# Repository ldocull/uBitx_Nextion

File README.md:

# uBitx_Nextion
This PCBA cleans up the wiring for V3-V5 uBitx Radio Kits that use the Nextion Display

Key features are:

 - [KB8CEC](https://github.com/phdlee) signal level meter and DSP functions are incorporated.
 - Anti-pop circuit was added to reduce the magnitude of key-clicks
 - Additional power supply filtering reduces background audio noise
 - Convenient points of connection for the Nextion display
 - Intermediate connections reduce wire harness

-[WR9R](http://wr9r.com/)

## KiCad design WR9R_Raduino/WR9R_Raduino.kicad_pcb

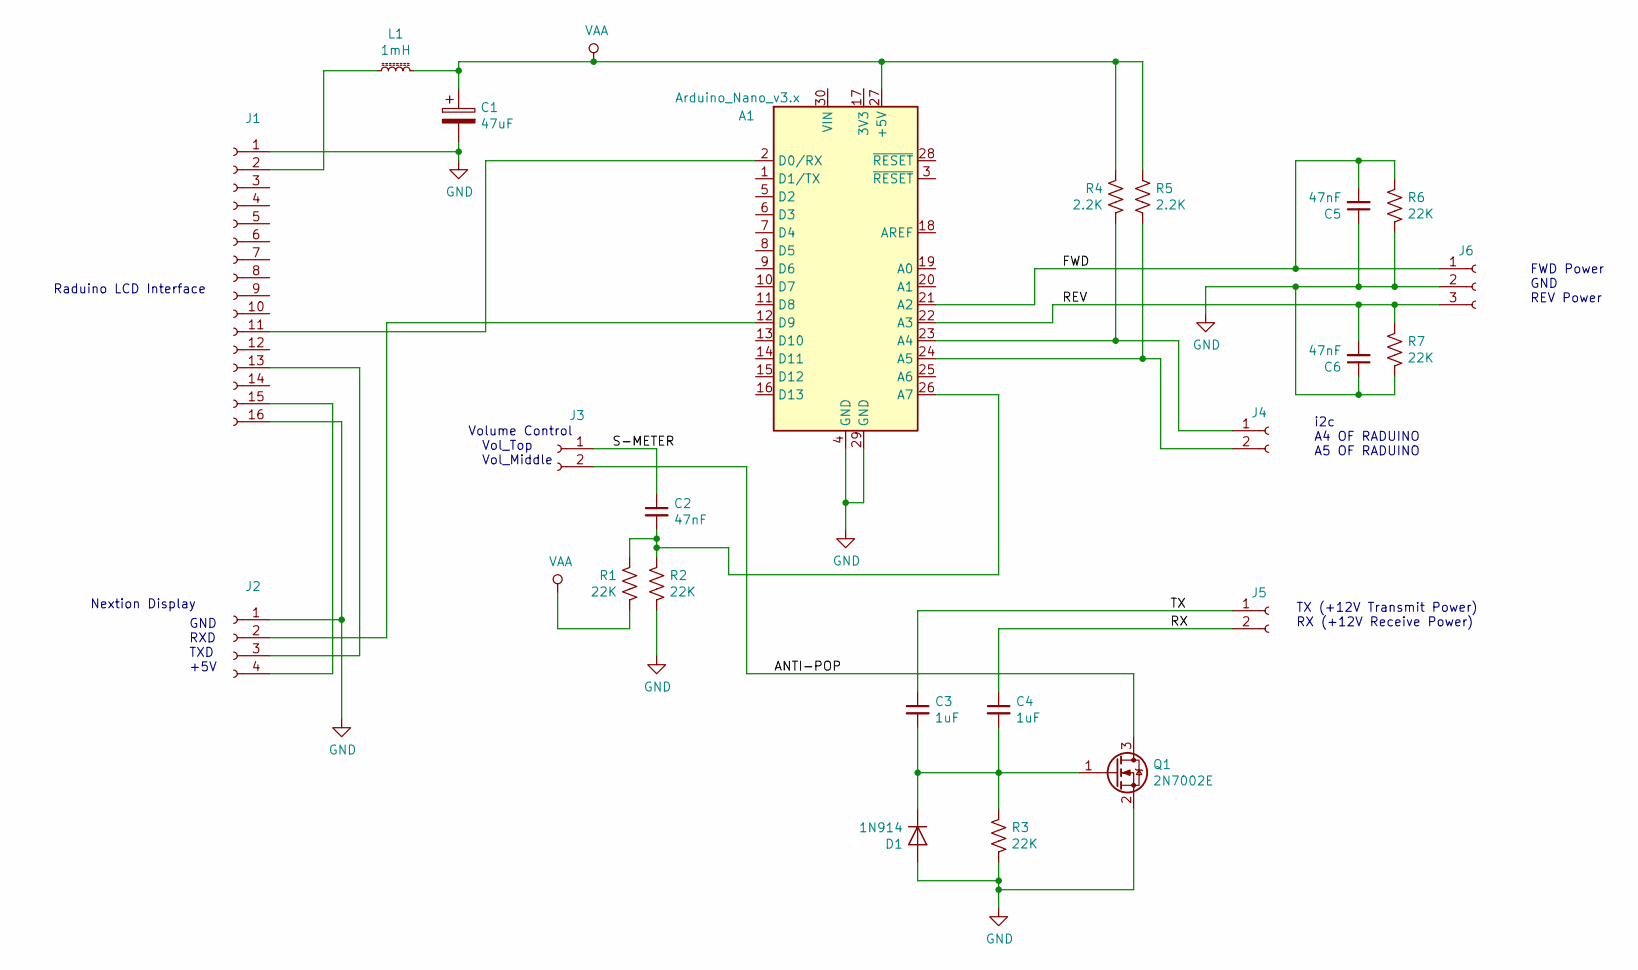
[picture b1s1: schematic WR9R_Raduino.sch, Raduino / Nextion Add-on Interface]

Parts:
A1: Arduino_Nano_v3.x; Arduino_Nano
C1: 47uF; CP_Radial_D4.0mm_P2.00mm
C2, C5, C6: 47nF; C_0805_2012Metric
C3, C4: 1uF; C_0805_2012Metric
D1: 1N914; D_DO-35_SOD27_P7.62mm_Horizontal
J1: Conn_01x16_Female; PinHeader_1x16_P2.54mm_Vertical
J2: Conn_01x04_Female; PinHeader_1x04_P2.54mm_Vertical
J3, J4, J5: Conn_01x02_Female; PinHeader_1x02_P2.54mm_Vertical
J6: Conn_01x03_Female; PinHeader_1x03_P2.54mm_Vertical
L1: 1mH; L_Radial_D8.7mm_P5.00mm_Fastron_07HCP
Q1: 2N7002E; SOT-23
R1, R2, R3, R6, R7: 22K; R_0805_2012Metric
R4, R5: 2.2K; R_0805_2012Metric

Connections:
/ANTI-POP: J3.2, Q1.3 (D)
/FWD: A1.21 (A2), C5.2, J6.1, R6.1
/REV: A1.22 (A3), C6.2, J6.3, R7.1
/RX: C4.1, J5.2
/S-METER: C2.1, J3.1
/TX: C3.1, J5.1
GND: A1.4 (GND), A1.29 (GND), C1.2, C5.1, C6.1, D1.2 (A), J1.1, J1.16, J2.1, J6.2, Q1.2 (S), R2.2, R3.2, R6.2, R7.2
unnamed: A1.2 (D0/RX), J1.11
unnamed: A1.12 (D9), J2.2
unnamed: A1.23 (A4), J4.1, R4.1
unnamed: A1.24 (A5), J4.2, R5.2
unnamed: A1.26 (A7), C2.2, R1.2, R2.1
unnamed: C3.2, C4.2, D1.1 (K), Q1.1 (G), R3.1
unnamed: J1.2, L1.1
unnamed: J1.13, J2.3
unnamed: J1.15, J2.4
VAA: A1.27 (+5V), C1.1, L1.2, R1.1, R4.2, R5.1

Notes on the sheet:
Raduino LCD Interface
Nextion Display
Volume Control Vol_Top Vol_Middle
FWD Power GND REV Power
TX (+12V Transmit Power) RX (+12V Receive Power)
GND RXD TXD +5V
i2c A4 OF RADUINO A5 OF RADUINO

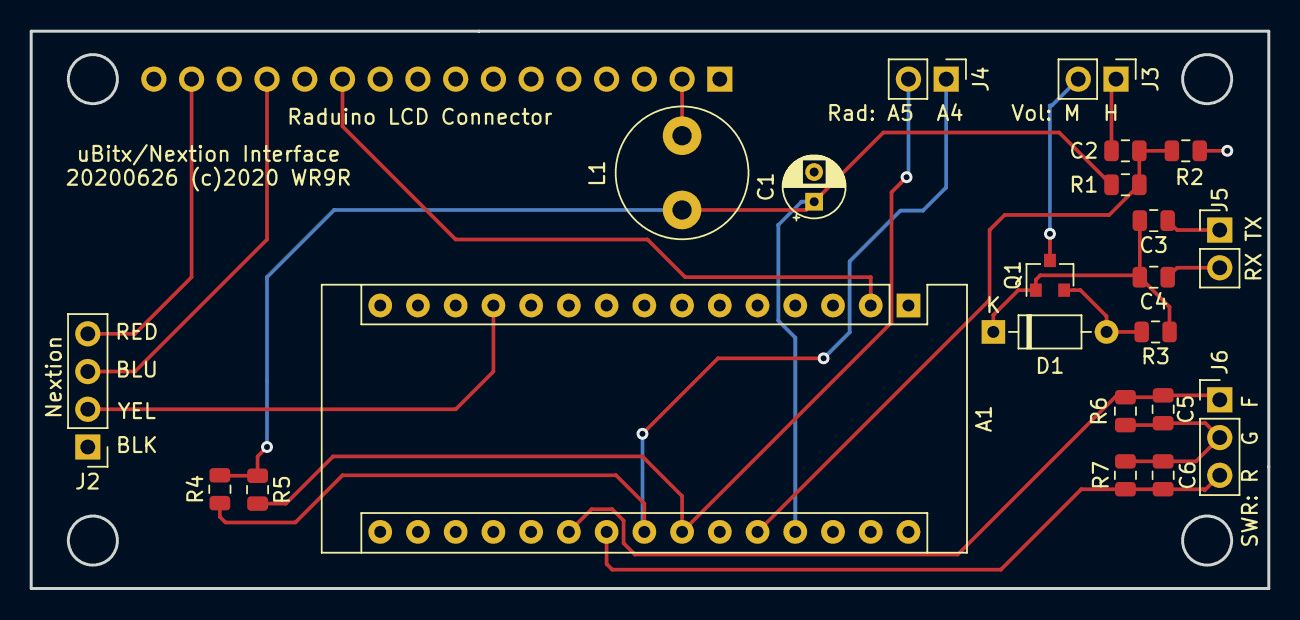
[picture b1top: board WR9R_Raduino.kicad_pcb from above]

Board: 2 copper layers, 83.3 x 37.5 mm, 23 parts (1 on the bottom side), 17 nets.

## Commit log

2020-08-10 KiCAD Project
    Schematics, Layout and Gerbers for the Raduino-Nextion Interface

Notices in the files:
WR9R_Raduino/WR9R_Raduino.kicad_pcb:
20200626 (c)2020 WR9R
